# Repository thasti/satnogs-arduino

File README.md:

SatNOGS Arduino
===============

Repository of Arduino code and Arduino PCB for SatNOGS project.
Refer to block diagram in the repository for wiring documentation.

Electronics and code are modified to work with a bare AtMega328p with the Arduino Bootloader. This spares buying the Arduino Micro. The stepper motor drivers are replaced by DRV8825 modules (Drop-in replacement part) from eBay.

This will be used in our costumized version of the SatNOGS PCB for the High Altitude Object Tracker, which will be part of the SatNOGS project as well.

# Flashing Instructions

Use the following command line to ISP the AtMega328p from an AVR910

avrdude -cavr910 -b115200 -P/dev/ttyUSB1 -pm328p -U lfuse:w:0xFF:m -U hfuse:w:0xDE:m -U efuse:w:0x05:m -v -x devcode=0x31

avrdude -pm328p -b115200 -cavr910 -x devcode=0x31 -P/dev/ttyUSB0 -U flash:w:SatNOGS.hex -v

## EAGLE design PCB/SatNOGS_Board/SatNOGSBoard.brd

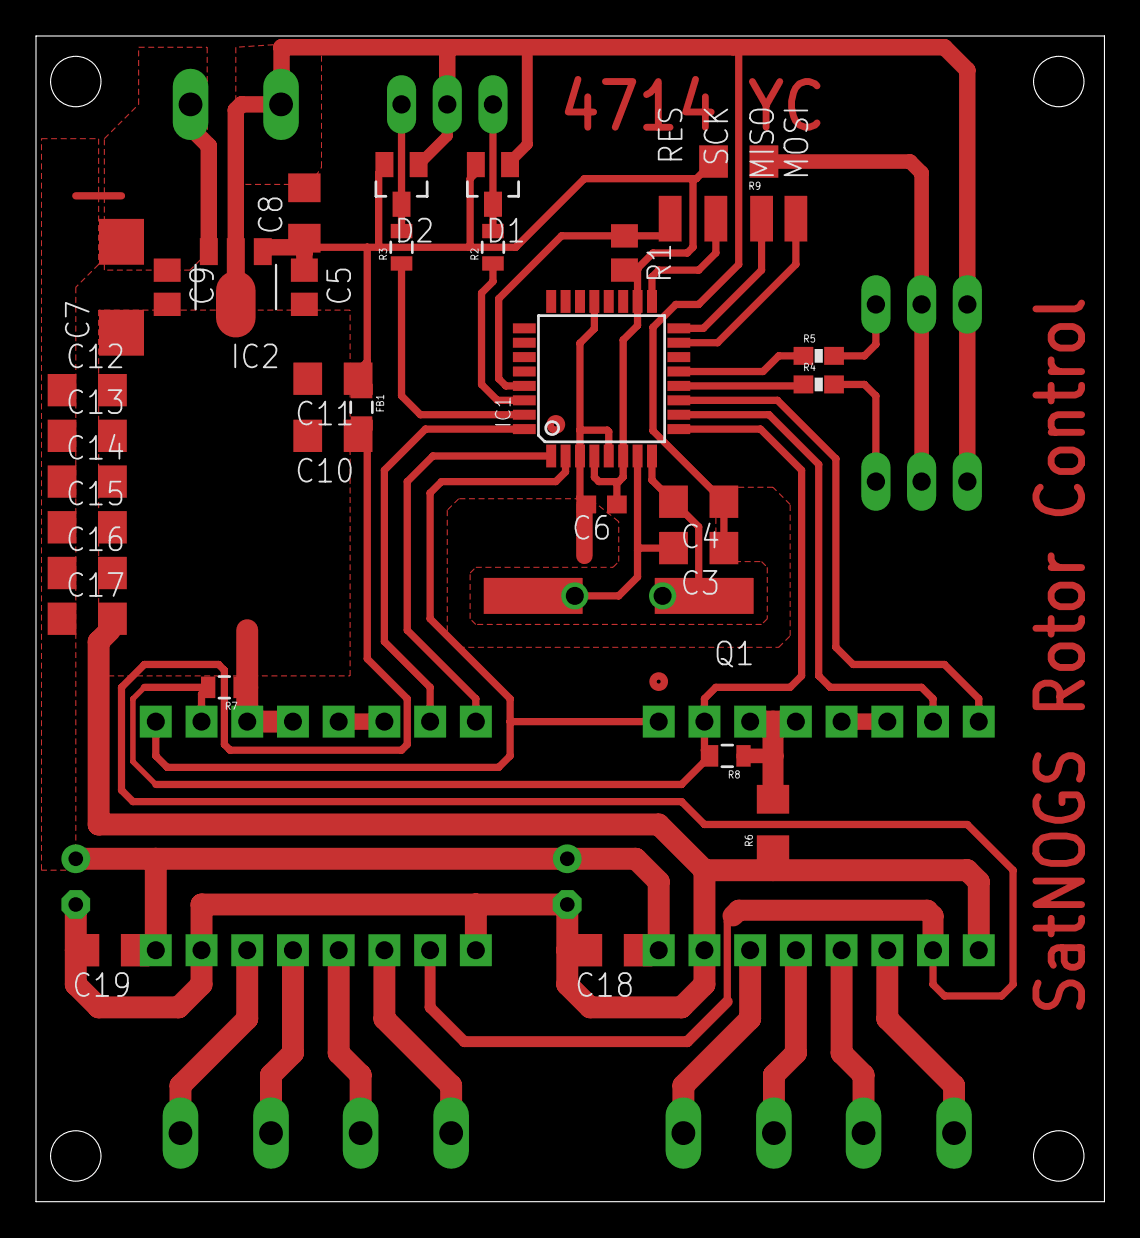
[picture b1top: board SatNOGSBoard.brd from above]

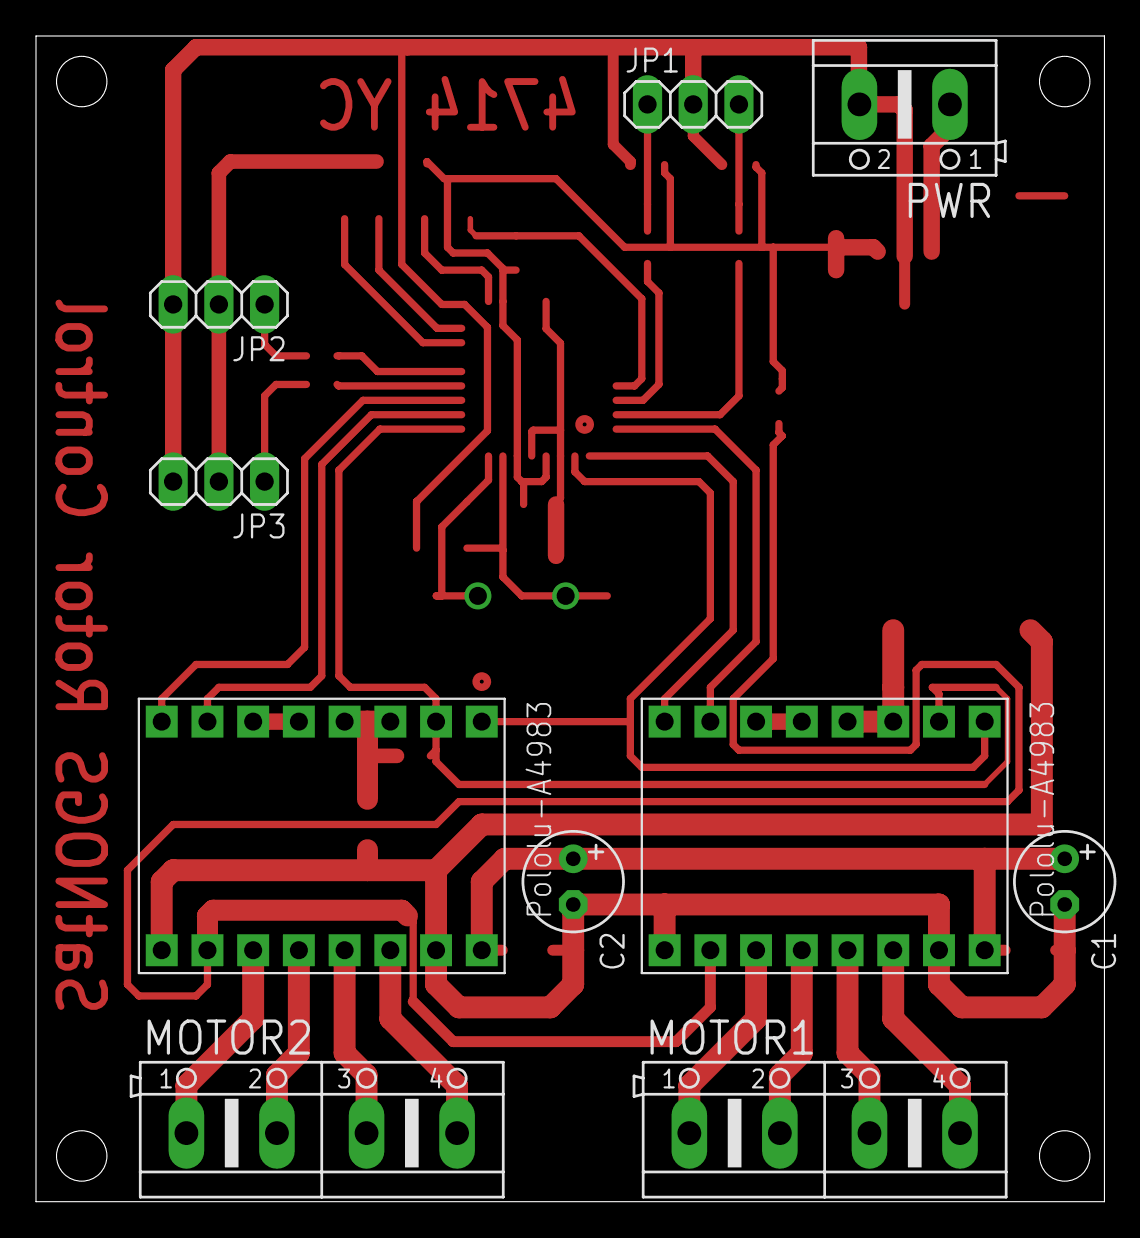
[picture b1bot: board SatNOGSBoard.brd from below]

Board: 2 copper layers, 59.4 x 64.8 mm, 46 parts (10 on the bottom side), 36 nets.

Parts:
C1, C2: 100uF; E2,5-6
C3, C4: 18p; C1206
C5, C9: 100n; C0805
C6: 100n; C0603
C7: C/6032-28R
C8, C10, C11, C12, C13, C14, C15, C16, C17, C18, C19: 680n; C1206
D1, D2: BAV99; SOT23
DRIVER1, DRIVER2: POLOLU-A4983POLOLU-A4983; POLOLU-A4983
FB1: 10R@100MHz; 0805
IC1: MEGA8-AI; TQFP32-08
IC2: 78L05F; SOT89
JP1, JP2, JP3: 1X03
MISO: SMD1,27-2,54
MOSI: SMD1,27-2,54
MOTOR1: 2; AK500/4
MOTOR2: 3; AK500/4
PWR: 1; AK500/2
Q1: 16MHz; CSM-7X-DU
R1: 4k7; R0805
R2: 1k; 0805
R3: 475R; 0805
R4, R5: 0603-RES
R6, R9: 0R; 1206
R7, R8: 100k; 0805
RES: SMD1,27-2,54
SCK: SMD1,27-2,54

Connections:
1-1A: DRIVER1.12, MOTOR1.2
1-1B: DRIVER1.11, MOTOR1.1
1-2A: DRIVER1.13, MOTOR1.3
1-2B: DRIVER1.14, MOTOR1.4
2-1A: DRIVER2.12, MOTOR2.2
2-1B: DRIVER2.11, MOTOR2.1
2-2A: DRIVER2.13, MOTOR2.3
2-2B: DRIVER2.14, MOTOR2.4
+5V: C5.1, C6.1, C8.1, C11.1, D1.2, D2.2, FB1.1, IC1.4, IC1.6, IC1.18, IC2.1, R1.2, R9.2
+5VM: C10.1, DRIVER1.10, DRIVER2.10, FB1.2
+12V: C1.+, C2.+, C7.+, C9.1, C12.1, C13.1, C14.1, C15.1, C16.1, C17.1, C18.1, C19.1, DRIVER1.16, DRIVER2.16, IC2.3, PWR.1
DIR-1: DRIVER1.8, IC1.1
DIR-2: DRIVER2.8, IC1.11
GND: C1.-, C2.-, C3.1, C4.1, C5.2, C6.2, C7.-, C8.2, C9.2, C10.2, C11.2, C12.2, C13.2, C14.2, C15.2, C16.2, C17.2, C18.2, C19.2, D1.1, D2.1, DRIVER1.3, DRIVER1.4, DRIVER1.9, DRIVER1.15, DRIVER2.9, DRIVER2.15, IC1.3, IC1.5, IC1.21, IC2.2, IC2.2@1, JP1.2, JP2.3, JP3.3, PWR.2, R6.1, R7.1
MS1: DRIVER1.2, DRIVER2.2, IC1.9, R7.2, R8.2
M_EN: DRIVER1.1, DRIVER2.1, IC1.2
unnamed: DRIVER1.5, DRIVER1.6
unnamed: DRIVER2.5, DRIVER2.6
unnamed: D1.3, JP1.1, R2.2
unnamed: D2.3, JP1.3, R3.2
unnamed: IC1.29, R1.1, RES.1
unnamed: IC1.30, R2.1
unnamed: IC1.31, R3.1
unnamed: IC1.13, R5.1
unnamed: IC1.15, MOSI.1
unnamed: IC1.16, MISO.1
unnamed: IC1.17, SCK.1
unnamed: IC1.12, R4.1
unnamed: DRIVER2.3, DRIVER2.4, R6.2, R8.1
unnamed: JP2.2, JP3.2, R9.1
STEP-1: DRIVER1.7, IC1.32
STEP-2: DRIVER2.7, IC1.10
SW1: JP2.1, R5.2
SW2: JP3.1, R4.2
XTAL1: C3.2, IC1.7, Q1.2
XTAL2: C4.2, IC1.8, Q1.1

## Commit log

2014-09-28 Add arduino code with homing function.
2014-10-07 Add homing function.
2014-10-08 Add homing function and homing command extension for easyCom 2.
2014-10-08 Remove backup file and update .gitignore .
2014-11-22 update README to describe repo
2014-11-22 add arduino pro micro pinout
2014-11-22 add AtMega48 Pin Mapping
2014-11-23 update pin assignments in Arduino code
    I don't know yet, wheter that change of pins will work.
2014-11-23 schematic update, raw routing prototype
    this adds the AtMega168 and neccesary components. Layout is just a raw
    sketch, someone should finish that.
2014-11-23 board routing
2014-11-23 correct pinout in Arduino code
2015-01-29 remove TODOs
2015-01-29 add flashing instructions

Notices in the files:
parts and their libraries:
SparkFun-Resistors: Licensing: CC v3.0 Share-Alike You are welcome to use this library for commercial purposes.
